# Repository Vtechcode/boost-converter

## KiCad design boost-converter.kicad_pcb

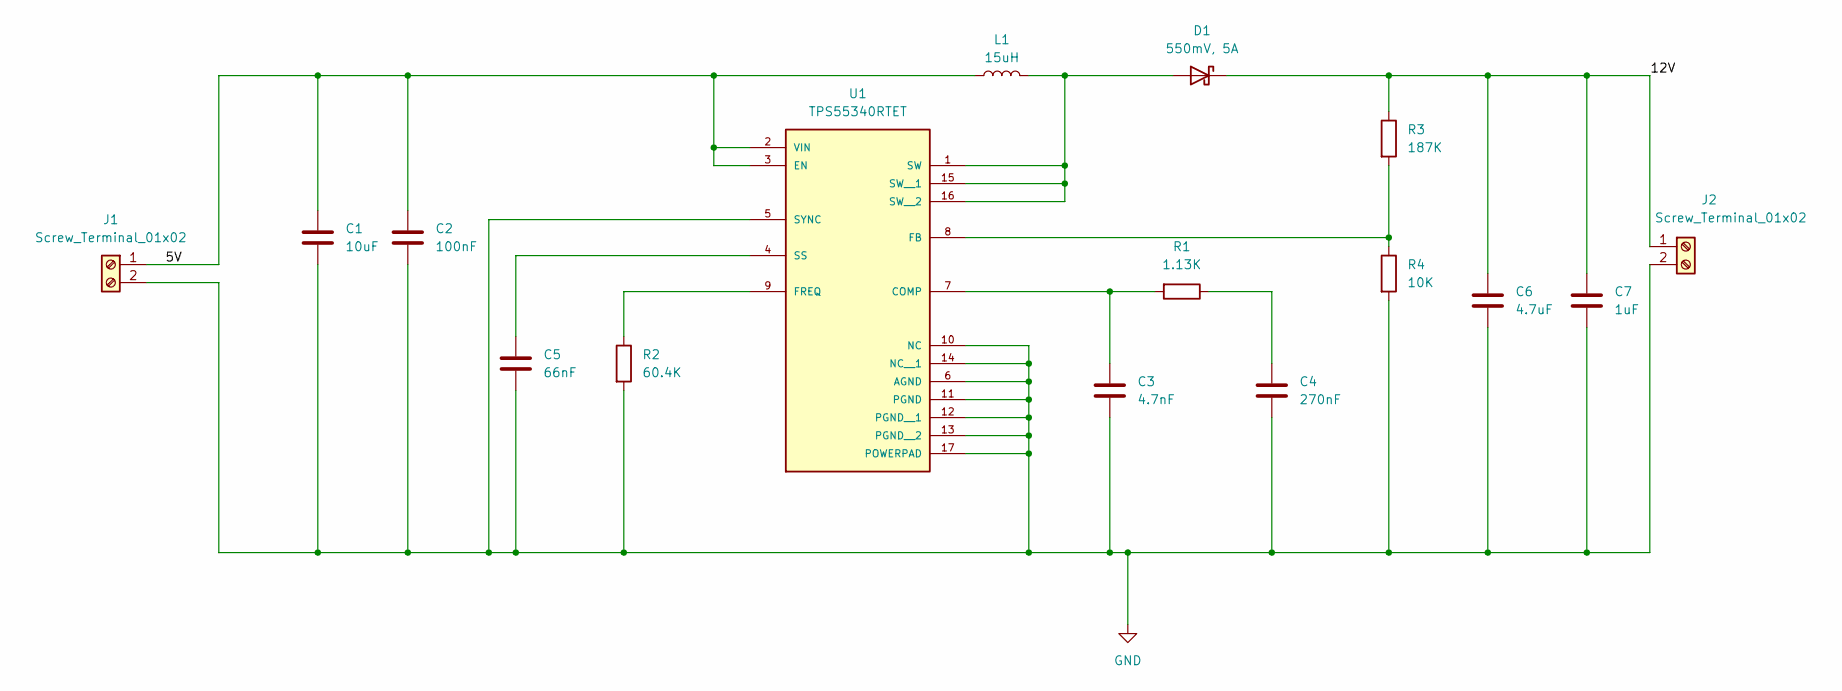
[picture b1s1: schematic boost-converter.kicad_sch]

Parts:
C1: 10uF; C_0603_1608Metric
C2: 100nF; C_0603_1608Metric
C3: 4.7nF; C_0603_1608Metric
C4: 270nF; C_0603_1608Metric
C5: 66nF; C_0603_1608Metric
C6: 4.7uF; C_0603_1608Metric
C7: 1uF; C_0603_1608Metric
D1: 550mV, 5A; D_3220_8050Metric_Pad2.65x5.15mm_HandSolder
J1, J2: Screw_Terminal_01x02; TerminalBlock_Phoenix_MPT-0,5-2-2.54_1x02_P2.54mm_Horizontal
L1: 15uH; L_Coilcraft_XAL1580-741
R1: 1.13K; R_0603_1608Metric
R2: 60.4K; R_0603_1608Metric
R3: 187K; R_0603_1608Metric
R4: 10K; R_0603_1608Metric
U1: TPS55340RTET; QFN50P300X300X80-17N

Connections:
/5V: C1.1, C2.1, J1.1, L1.1, U1.2 (VIN), U1.3 (EN)
/12V: C6.1, C7.1, D1.1 (K), J2.1, R3.1
GND: C1.2, C2.2, C3.2, C4.2, C5.2, C6.2, C7.2, J1.2, J2.2, R2.2, R4.2, U1.5 (SYNC), U1.6 (AGND), U1.10 (NC), U1.11 (PGND), U1.12 (PGND__1), U1.13 (PGND__2), U1.14 (NC__1), U1.17 (POWERPAD)
unnamed: C4.1, R1.1
unnamed: D1.2 (A), L1.2, U1.1 (SW), U1.15 (SW__1), U1.16 (SW__2)
unnamed: C3.1, R1.2, U1.7 (COMP)
unnamed: R3.2, R4.1, U1.8 (FB)
unnamed: R2.1, U1.9 (FREQ)
unnamed: C5.1, U1.4 (SS)

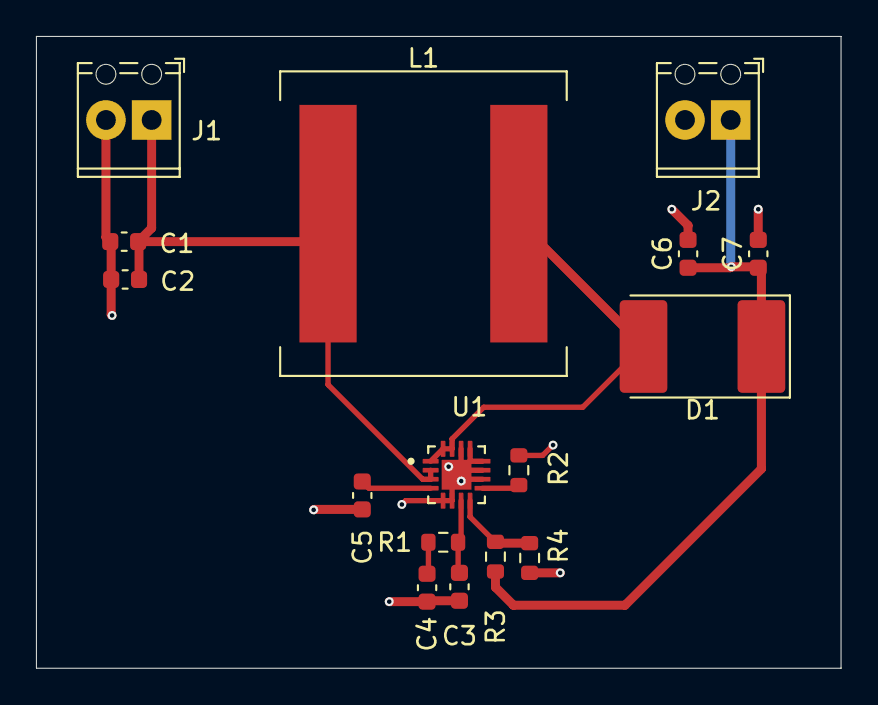
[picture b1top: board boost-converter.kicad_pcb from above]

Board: 2 copper layers, 44.7 x 35.1 mm, 16 parts (0 on the bottom side), 9 nets.

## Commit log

2025-07-29 done schematic
2025-08-04 Done up to pcb layout and routing
